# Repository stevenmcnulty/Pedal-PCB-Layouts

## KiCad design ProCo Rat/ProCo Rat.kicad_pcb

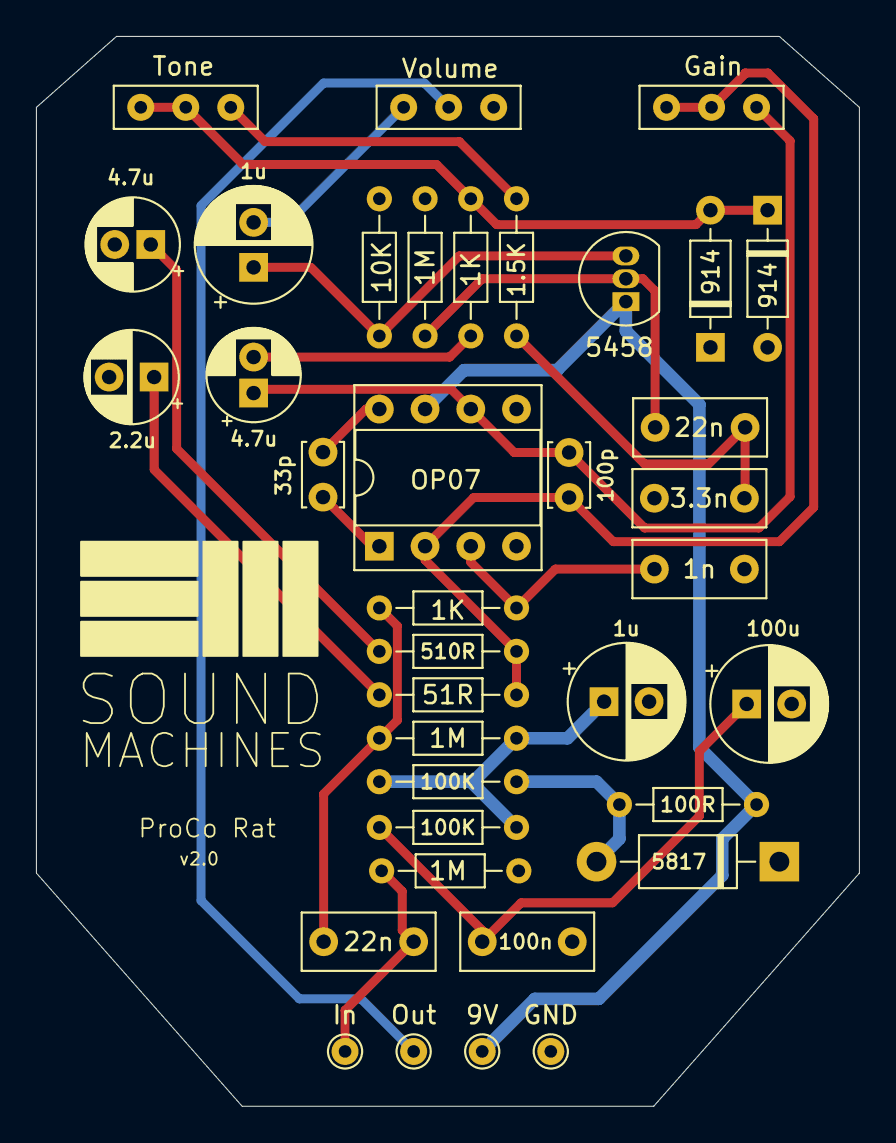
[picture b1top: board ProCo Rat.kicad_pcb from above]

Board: 2 copper layers, 45.7 x 59.4 mm, 37 parts (0 on the bottom side), 22 nets.

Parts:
1.5K: 1.5K; THT Standard Resistor
1K, 1K#2: 1K; THT Standard Resistor
1M, 1M#2, 1M#3: 1M; THT Standard Resistor
1n: 1n; Film Capacitor (L7.2_W3.0_P5.0)
1u, 1u#2: 1u; Electrolytic Capacitor (D6.3_P2.5)
2.2u: 2.2u; Electrolytic Capacitor (D5_P2.5)
3.3n: 3.3n; Film Capacitor (L7.2_W3.0_P5.0)
4.7u, 4.7u#2: 4.7u; Electrolytic Capacitor (D5.0_P2.0)
9V: 9V; 1 Wire Pad
10K: 10K; THT Standard Resistor
22n, 22n#2: 22n; Film Capacitor (L7.2_W3.0_P5.0)
33p: 33p; Ceramic Disc Capacitor (P2.5)
51R: 51R; THT Standard Resistor
100K, 100K#2: 100K; THT Standard Resistor
100R: 100R; THT Standard Resistor
100n: 0.1u; Film Capacitor (L7.2_W3.0_P5.0)
100p: 100p; Ceramic Disc Capacitor (P2.5)
100u: 100u; Electrolytic Capacitor (D6.3_P2.5)
510R: 510R; THT Standard Resistor
914, 914#2: 1N914; D_DO-35_SOD27_P7.62mm_Horizontal
5458: 2N5458; TO-92_Inline
5817: 1N5817; D_DO-41_SOD81_P10.16mm_Horizontal
GND: GND; 1 Wire Pad
Gain: A100K; 3 Wire Pads
In: Input; 1 Wire Pad
OP07: OP07; DIP-8 Socketed
Out: Output; 1 Wire Pad
Tone: A100K; 3 Wire Pads
Volume: A100K; 3 Wire Pads

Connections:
+4.5V: 1M.1, 1u.1, 100K.1, 100K#2.2
+9V: 9V.1, 100R.1, 5458.1 (C), OP07.7 (V+)
GND: 1M#2.2, 1M#3.2, 1n.1, 1u.2, 2.2u.2, 3.3n.2, 4.7u#2.2, 10K.2, 100n.2, 100u.2, 914.1 (K), 914#2.2 (A), 5817.1 (K), GND.1, OP07.4 (V-), Volume.3
unnamed: 1M#3.1, 22n#2.1, In.1
unnamed: 1K#2.1, 1M.2, 22n#2.2
unnamed: 100K.2, 100n.1, 100u.1
unnamed: 33p.1, OP07.1 (VOS)
unnamed: 33p.2, OP07.8 (VOS)
unnamed: 2.2u.1, 51R.2
unnamed: 4.7u#2.1, 510R.2
unnamed: 4.7u.1, 100p.1, Gain.3, OP07.6
unnamed: 1K.1, 4.7u.2
unnamed: 1.5K.2, 3.3n.1, 22n.1
unnamed: 1u#2.2, Volume.1
unnamed: 100K#2.1, 100R.2, 5817.2 (A)
unnamed: 1K.2, 914.2 (A), 914#2.1 (K), Tone.1, Tone.2
unnamed: Out.1, Volume.2
unnamed: 1.5K.1, Tone.3
unnamed: 1M#2.1, 22n.2, 5458.2 (B)
unnamed: 1u#2.1, 10K.1, 5458.3 (E)
unnamed: 1K#2.2, 1n.2, OP07.3 (+)
unnamed: 51R.1, 100p.2, 510R.1, Gain.1, Gain.2, OP07.2 (-)
